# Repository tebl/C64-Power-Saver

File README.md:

# C64 Power Saver
This is a project I started a few years back after buying the components to build one from console5.com, but as so many of them I didn't take it past the breadboard and ended up with yet another pile of components that sort of works. Now, with a few rainy days past I've finally found the time to draw it out in KiCAD and make a few boards for this project - the first one I used the wrong pinouts so I made a PCB saver that only connects with bad power supplies, then I made one that melted. Third times the charm and this one is working great, so might have to start looking into building a bunch of them for the rest of my C64s.

Why you'd need one in the first place, you say? Basically, Commodore intended the computer to live a maximum of 5-6 years and so the components chosen reflected this - no thought went into considering what happens past this point. Now that it's 30 years later we know that the 5v regulator has a tendency to short out input and output voltage, meaning that those sensitive 5v chips will intermittenly, or sometimes even permanently, end up getting something like two or three times that... enough to melt that precious silicon! Your options are either to get a brand new power supply or combine your old one with a C64 power saver for as long as that'll still be around, running unprotected is simply foolish these days!

How does it work? The design is based on the one developed by famed C64-tinkerer Ray Carlsen, what it does is monitor the 5v line coming from your power supply and when it starts outputting voltages above 5.6v a relay is slammed shut and the line is cut. You have the option of mounting a buzzer to the board so that you can get annoyed at it until you realize it's time to buy or build a new PSU, or when mounted externally you can look at the nice LEDs to figure out wether your supply is good or not. Once a PSU has started to go bad, put a "Bad PSU" sticker on it and never use it again! For details on where to cut and solder internally on the computer see Ray Carlsens [website](http://personalpages.tds.net/~rcarlsen/cbm/c64/SAVER/MOBOs/).

## Errata
**Revision C/D**
It has come to my attention that some original Commodore 64 power supplies were wired differently, specifically sometimes 5v would be supplied on the opposite pin - this is easily fixed by connecting a small piece of wire across DIN pins 4 and 5. Refer to this [image](https://github.com/tebl/C64-Power-Saver/raw/master/gallery/revision_d_fix.PNG), the board outline is shown from above and the wire you need to add is the green one.

# Schematic
The supplied KiCad files should be sufficient as both a schematic and as a  starting point for ordering PCBs (basically you could just zip the contents of the export folder and upload that on a fabrication site), the schematic is also available in [PDF-format](https://github.com/tebl/C64-Power-Saver/raw/master/export/C64%20Power%20Saver.pdf) and this is what you'll need to print and work your way through this things don't work as expected after assembly.

# BOM
Most parts should be easy to get a hold of from your favourite local electronic component shop though you might have to consider other sources for the older parts such as the CPU and memory. Personally I bought most components with free shipping from China via AliExpress - prices will vary, but I found everything in larger quantities than needed for the cost of a few cups of fancy coffee! Last couple of components listed are for making the cable that goes from the power saver and into your C64, not needed if the module is to be mounted internally in the computer.

| Reference    | Item                                  | Count |
| ------------ | ------------------------------------- | ----- |
| PCB          | Fabricate using Gerber files ([order](https://www.pcbway.com/project/shareproject/W217819ASN17_C64_Power_Saver.html?inviteid=88707))  |     1 |
| D1           | 1N4732A DO-35                         |     1 |
| D2           | 1N4148 DO-35, alternatively 1N914     |     1 |
| D3           | 5mm LED (green)                       |   (1) |
| D4           | 5mm LED (red)                         |     1 |
| F1           | Fuse holder, with 1A fast acting fuse |     1 |
| J5           | 7pin DIN socket PCB mount             |   (1) |
| K1           | SRD-5VDC-SL-C 5v relay                |     1 |
| Q1, Q2       | 2N2222 TO-92 transistor               |     2 |
| R1,R2,R4,R5  | 470 ohm resistor                      |     4 |
| R3           | 2k2 ohm (2200) resistor               |     1 |
| BZ1          | 5v active buzzer, 7.6mm pin spacing   |     1 |
|              | 4-core wire                           |   (1) |
|              | 7pin male DIN plug                    |   (1) |
|              | 70x45x30mm electronic project box     |   (1) |

Please use the order link above when signing up to help me support this project, I'll get a small discount on future orders and hopefully that means I can afford to keep developing new and exciting modules in the future. By using the URL you won't have to deal with the rather daunting order forms for PCB fabrication, but if you want to go that route they'll probably want a zipped-up copy of the files in the export-directory!

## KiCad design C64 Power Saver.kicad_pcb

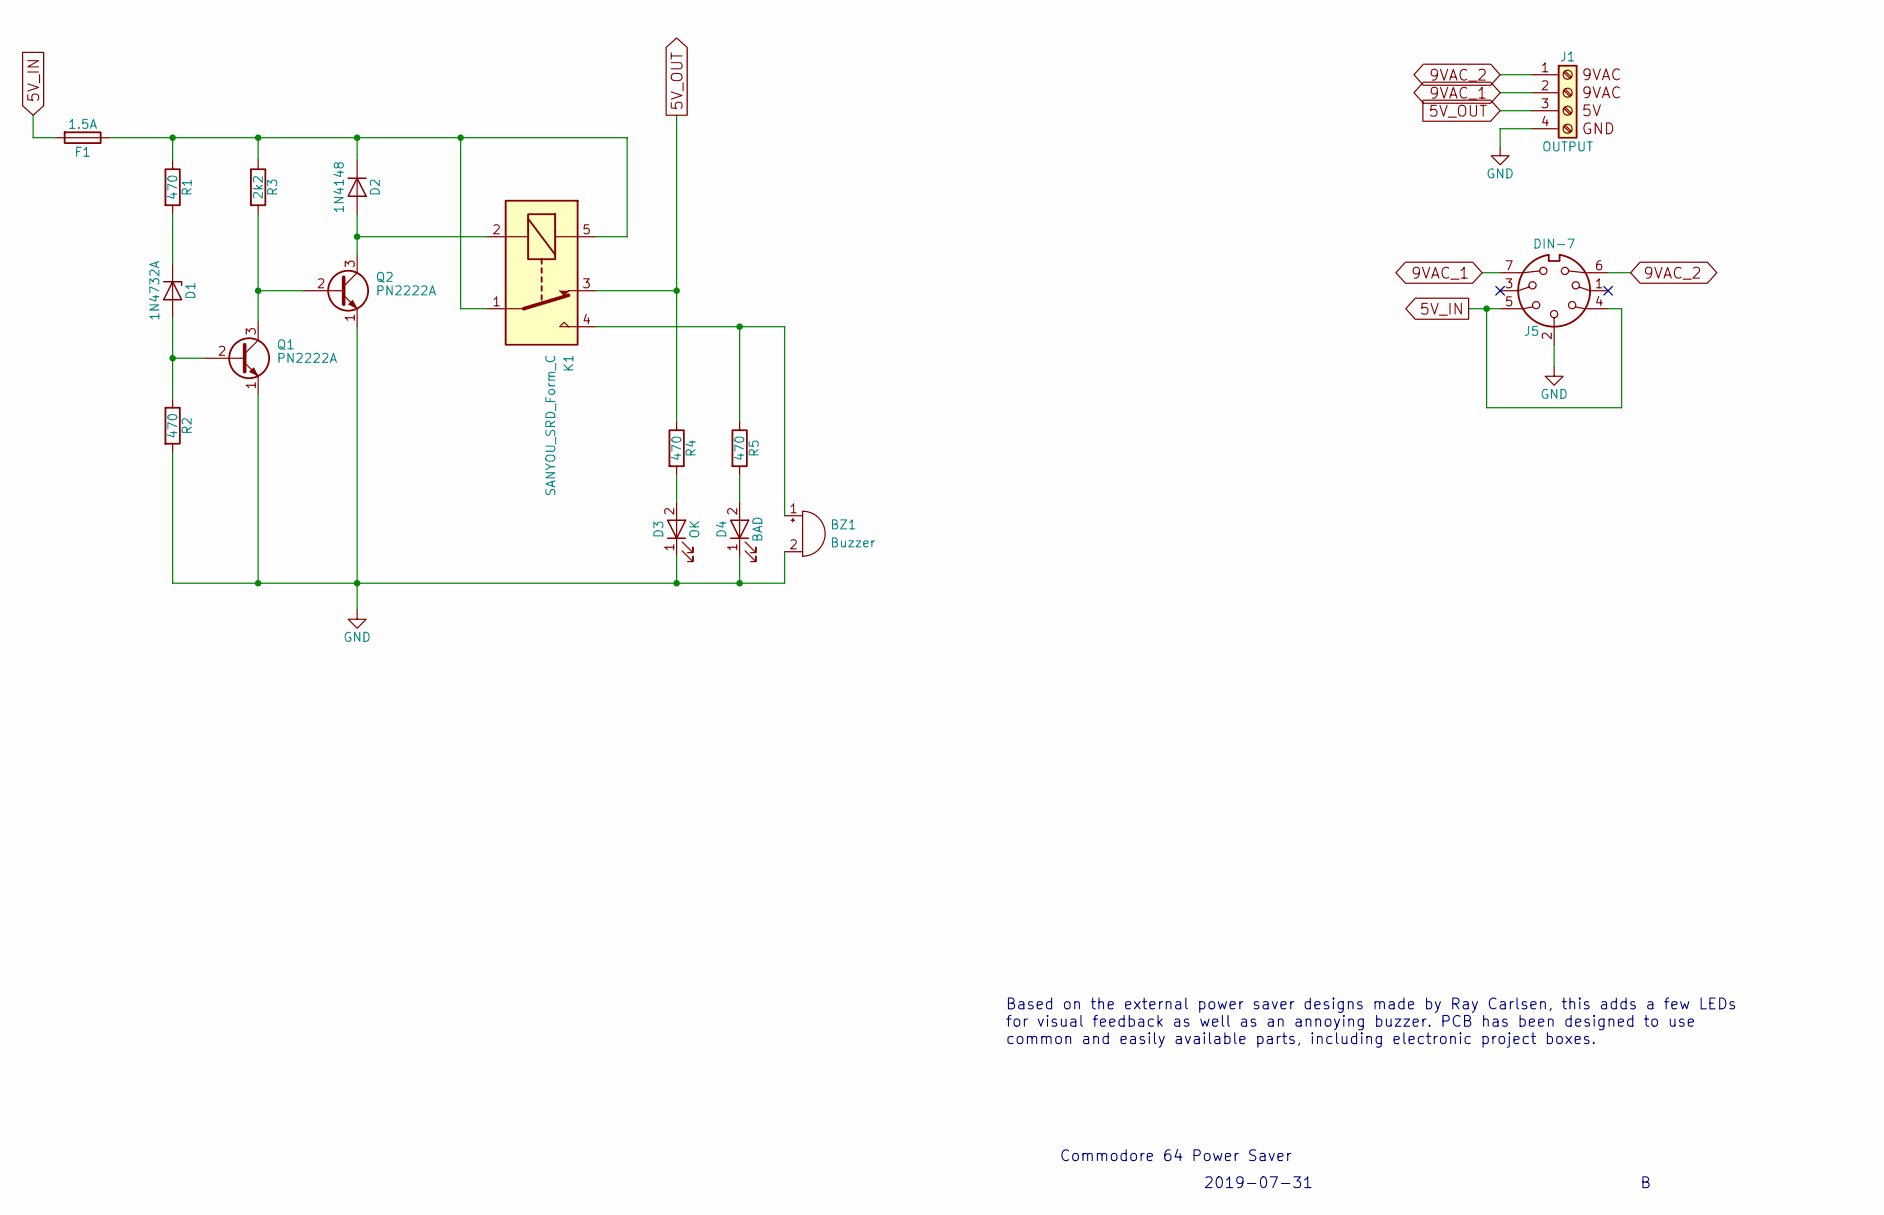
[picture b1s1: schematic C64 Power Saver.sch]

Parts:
BZ1: Buzzer; Buzzer_12x9.5RM7.6
D1: 1N4732A; D_T-1_P10.16mm_Horizontal
D2: 1N4148; D_DO-35_SOD27_P10.16mm_Horizontal
D3: OK; LED_D5.0mm
D4: BAD; LED_D5.0mm
F1: 1.5A; Fuseholder5x20_horiz_SemiClosed_Casing10x25mm
J1: OUTPUT; OUTPUT_ZIP
J5: DIN-7; C64_PWR
K1: SANYOU_SRD_Form_C; Relay_SPDT_SANYOU_SRD_Series_Form_C
Q1, Q2: PN2222A; TO-92_Inline_Wide
R1, R2, R4, R5: 470; R_Axial_DIN0207_L6.3mm_D2.5mm_P10.16mm_Horizontal
R3: 2k2; R_Axial_DIN0207_L6.3mm_D2.5mm_P10.16mm_Horizontal

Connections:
5V_IN: F1.2, J5.4, J5.5
5V_OUT: J1.3, K1.3, R4.1
9VAC_1: J1.2, J5.7
9VAC_2: J1.1, J5.6
GND: BZ1.2 (+), D3.1 (K), D4.1 (K), J1.4, J5.2, Q1.1 (E), Q2.1 (E), R2.2
unnamed: BZ1.1 (-), K1.4, R5.1
unnamed: D1.1 (K), R1.2
unnamed: D1.2 (A), Q1.2 (B), R2.1
unnamed: D2.1 (K), F1.1, K1.1, K1.5, R1.1, R3.1
unnamed: D2.2 (A), K1.2, Q2.3 (C)
unnamed: D3.2 (A), R4.2
unnamed: D4.2 (A), R5.2
unnamed: Q1.3 (C), Q2.2 (B), R3.2

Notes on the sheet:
Commodore 64 Power Saver
Based on the external power saver designs made by Ray Carlsen, this adds a few LEDs for visual feedback as well as an annoying buzzer. PCB has been designed to use common and easily available parts, including electronic project boxes.
2019-07-31

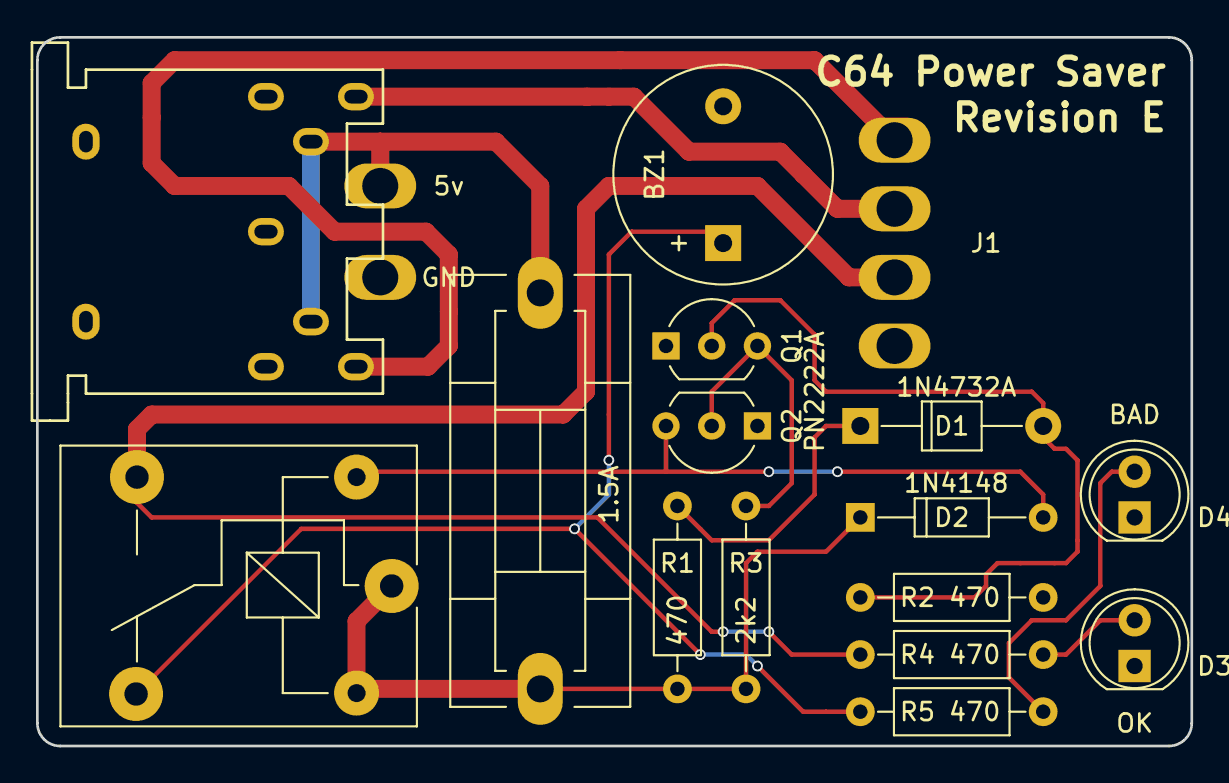
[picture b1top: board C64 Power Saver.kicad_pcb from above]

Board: 2 copper layers, 64.1 x 39.4 mm, 16 parts (0 on the bottom side), 13 nets.

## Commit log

2018-09-02 Basic schematic completed
2018-09-02 Added screw terminals for 9VAC
2018-09-02 PCB layout done
2018-09-02 DIN connector sketch (pads need measuring)
2018-09-02 Gerber export (without 7 pin din)
2018-09-26 Oh... So I made a saver that works only on bad ones... Rev. B!
2018-09-30 Updated schematic to use DIN connector and wire points
2018-09-30 PCB layout redone with DIN connector and added 5v buzzer
2018-10-15 Fixed groundplane and made wire solder points larger
2018-11-08 Added wire pads for +5v and GND for thicker wires when internal mounting
2018-11-08 Added gallery pictures
2018-11-08 Updated readme with BOM and images
2018-11-08 Added project box to BOM
2018-11-08 Added proper PCB link
2019-07-31 Added revision D fix image
2019-07-31 Add 5v to DIN-7 pin 4
2019-07-31 Updated errata section
2019-07-31 Updated gerbers
